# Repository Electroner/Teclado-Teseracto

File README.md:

# Teclado Personalizado en Español + PCB  

En este repositorio encontraras desde los datasheet de cada parte que he usado hasta los archivos originales del autocad, con todos los archivos descargados deberias ser capaz de poder crear y manufacturar este teclado sin ningun problema.

Este teclado usa un Atmega32u4 como controllador y un decodificador/Demultiplexor CD74HC154 4-a-16, Suficiente para conseguir un tiempo de respuesta igual o superior a los mejores teclados comerciales actuales (1060Hz).Pruebas realizadas con el codigo actual. Ademas se ha decido "prescindir" de un teclado numerico real, y lo que se ha hecho es conectar los numeros del numpad a  los numeros de la parte superior del teclado, por lo que las teclas tanto del numpad como los de la parte superior son los mismas, al igual con el intro y "." (Ver Esquematica).

Para el cuerpo y Plate se ha optado por una fabricacion completa de metacrilato atornillada de extremo a extremo con 28 tornillos que provocaran una sujeccion y una robustez sin igual. El diseño en todo momento de cada parte se ha realizado pensando en su mantenimiento y facilidad de reparacion.

Se ha actualizado a la version N-keyRollOver con unas modificaciones en las librerias de Keyboard.h y Keyboard.cpp

## Imagenes

Teclado Finalizado (No leds):

Teclado Finalizado (Leds):

Componentes de la PCB:

Vista Previa de la PCB:

Schematic:

Plano Plancha Superior (Plate):

## Recursos Usados

-   [Alguna Investigacion y aprendizaje](https://github.com/w4ilun/pocket-keyboard)

Y varias paginas para datos concretos como funciones en eagle,ayuda con el bootloader y ejemplos de otros teclados.

-   [Ayuda con el bootloader](https://forum.arduino.cc/t/burning-bootloader-to-custom-board-atmega32u4/890015)
-   [Ayuda con el N-key](https://forum.arduino.cc/t/how-to-program-n-key-rollover-atmega32u4/938418)

## Software Usado

-   [Editor de Layaout Teclado](http://www.keyboard-layout-editor.com/)
-   [Autocad](https://www.autodesk.es/products/autocad/overview?term=1-YEAR&tab=subscription)
-   [FreeCad](https://www.freecadweb.org/)
-   [Eagle](https://www.autodesk.com/products/eagle/free-download)
-   [Componentes Eagle](https://componentsearchengine.com/)
-   [Produccion de la PCB](https://jlcpcb.com/)
-   [Compra de los componentes](https://lcsc.com/)
-   [Corte de metacrilato (Tienda Local)](https://ecoplasticlaser.com/)

## Instalacion y Compilacion

Recomiendo el Arduino 1.8 (Legacy IDE (1.8.X)) en su version portable. 
Para poder compilar la placa y añadir los archivos personalizados vamos a seguir estos pasos:

1. En ./hardware/ meteremos la carpeta CLMKeyboard donde estan los archivos personalizados.
2. Dentro de las librerias (./libraries/Keyboard) vamos a sustituir los archivos keyboard.c y Keyboard.h
3. Dentro de arduino deberia aparacer nuestra Placa como CLM Keyboard.
4. Compilamos y subimos.

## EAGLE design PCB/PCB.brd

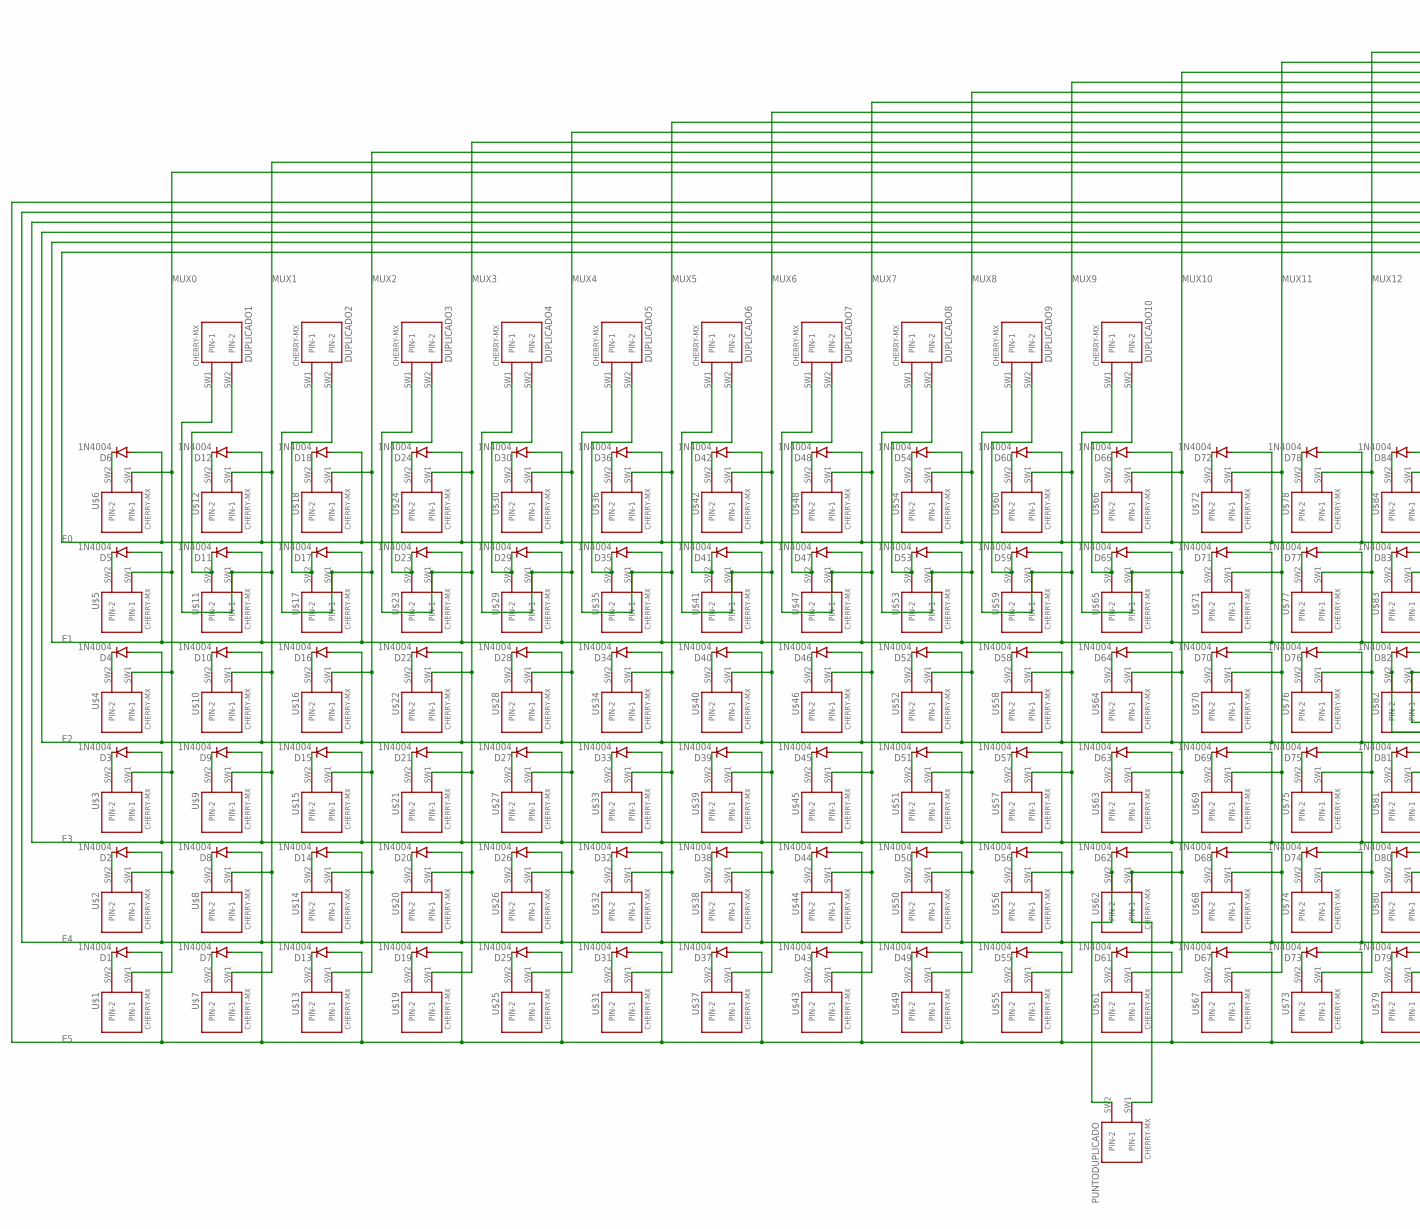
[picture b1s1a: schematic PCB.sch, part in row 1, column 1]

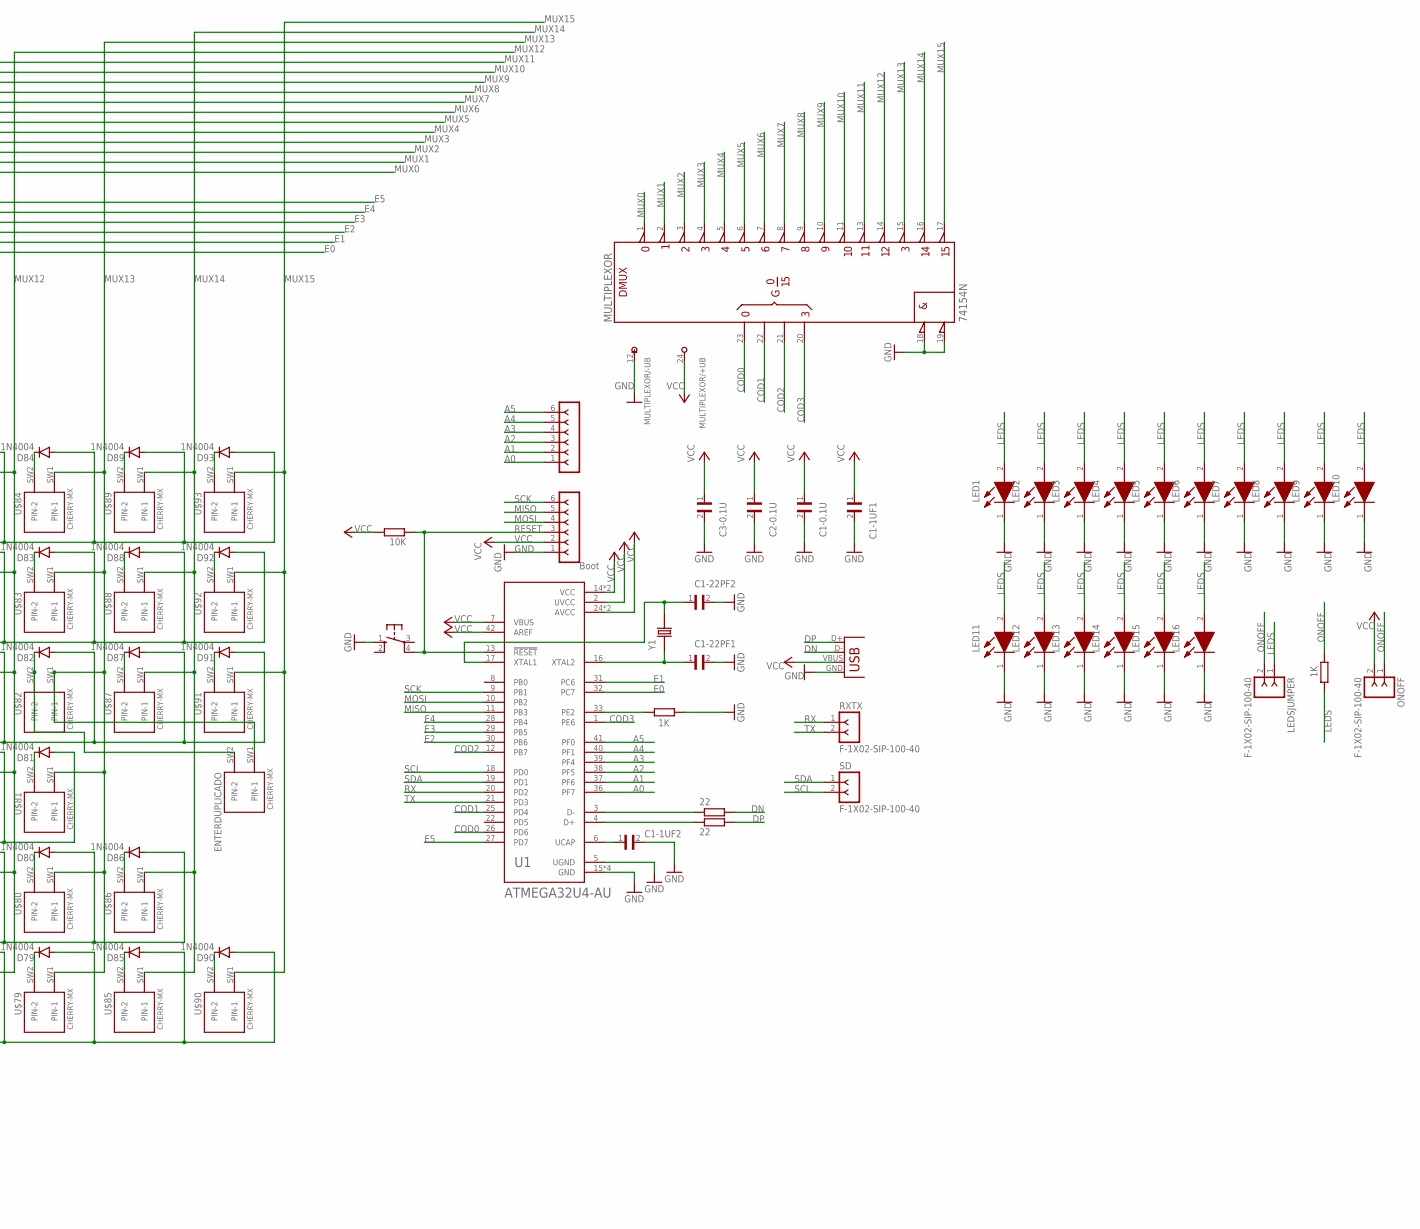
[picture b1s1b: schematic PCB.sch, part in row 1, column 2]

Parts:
ANALOG: Boot; SIP-100-06-32
BUTTON: 10-XX; B3F-10XX
C1-0.1U, C1-1UF1, C1-1UF2, C1-22PF1, C1-22PF2, C2-0.1U, C3-0.1U: RDE5C1H273J2M1H03A; CAP_RDE5C1H273J2M1H03A
D1, D2, D3, D4, D5, D6, D7, D8, D9, D10, D11, D12, D13, D14, D15, D16, D17, D18, D19, D20, D21, D22, D23, D24, D25, D26, D27, D28, D29, D30, D31, D32, D33, D34, D35, D36, D37, D38, D39, D40, D41, D42, D43, D44, D45, D46, D47, D48, D49, D50, D51, D52, D53, D54, D55, D56, D57, D58, D59, D60, D61, D62, D63, D64, D65, D66, D67, D68, D69, D70, D71, D72, D73, D74, D75, D76, D77, D78, D79, D80, D81, D82, D83, D84, D85, D86, D87, D88, D89, D90, D91, D92, D93: 1N4004; DO41-10
DUPLICADO1, DUPLICADO2, DUPLICADO3, DUPLICADO4, DUPLICADO5, DUPLICADO6, DUPLICADO7, DUPLICADO8, DUPLICADO9, DUPLICADO10: CHERRY-MX
ENTERDUPLICADO: CHERRY-MX
J3: Boot; SIP-100-06-32
LED1, LED2, LED3, LED4, LED5, LED6, LED7, LED8, LED9, LED10, LED11, LED12, LED13, LED14, LED15, LED16: ASMM-CA03-AS402; LEDM3528X200N
LEDSJUMPER: F-1X02-SIP-100-40; SIP-100-02-40
MULTIPLEXOR: 74154N; DIL24-3
ONOFF: F-1X02-SIP-100-40; SIP-100-02-40
PUNTODUPLICADO: CHERRY-MX
R1, R2: 22; 0204/7
R3, R4: 1K; 0204/7
R5: 10K; 0204/7
RXTX: F-1X02-SIP-100-40; SIP-100-02-40
SD: F-1X02-SIP-100-40; SIP-100-02-40
U1: ATMEGA32U4-AU; QFP80P1200X1200X120-44N
U$1, U$2, U$3, U$4, U$5, U$6, U$7, U$8, U$9, U$10, U$11, U$12, U$13, U$14, U$15, U$16, U$17, U$18, U$19, U$20, U$21, U$22, U$23, U$24, U$25, U$26, U$27, U$28, U$29, U$30, U$31, U$32, U$33, U$34, U$35, U$36, U$37, U$38, U$39, U$40, U$41, U$42, U$43, U$44, U$45, U$46, U$47, U$48, U$49, U$50, U$51, U$52, U$53, U$54, U$55, U$56, U$57, U$58, U$59, U$60, U$61, U$62, U$63, U$64, U$65, U$66, U$67, U$68, U$69, U$70, U$71, U$72, U$73, U$74, U$75, U$76, U$77, U$78, U$79, U$80, U$81, U$82, U$83, U$84, U$85, U$86, U$87, U$88, U$89, U$90, U$91, U$92, U$93: CHERRY-MX
X2: USB-A-H
Y1: ECS-160-20-4X; XTAL_ECS-160-20-4X

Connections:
A0: ANALOG.1, U1.36 (PF7)
A1: ANALOG.2, U1.37 (PF6)
A2: ANALOG.3, U1.38 (PF5)
A3: ANALOG.4, U1.39 (PF4)
A4: ANALOG.5, U1.40 (PF1)
A5: ANALOG.6, U1.41 (PF0)
COD0: MULTIPLEXOR.23 (A), U1.26 (PD6)
COD1: MULTIPLEXOR.22 (B), U1.25 (PD4)
COD2: MULTIPLEXOR.21 (C), U1.12 (PB7)
COD3: MULTIPLEXOR.20 (D), U1.1 (PE6)
D+: R1.1, U1.4 (D+)
D-: R2.1, U1.3 (D-)
DN: R2.2, X2.D-
DP: R1.2, X2.D+
E0: D6.A, D12.A, D18.A, D24.A, D30.A, D36.A, D42.A, D48.A, D54.A, D60.A, D66.A, D72.A, D78.A, D84.A, D89.A, D93.A, U1.32 (PC7)
E1: D5.A, D11.A, D17.A, D23.A, D29.A, D35.A, D41.A, D47.A, D53.A, D59.A, D65.A, D71.A, D77.A, D83.A, D88.A, D92.A, U1.31 (PC6)
E2: D4.A, D10.A, D16.A, D22.A, D28.A, D34.A, D40.A, D46.A, D52.A, D58.A, D64.A, D70.A, D76.A, D82.A, D87.A, D91.A, U1.30 (PB6)
E3: D3.A, D9.A, D15.A, D21.A, D27.A, D33.A, D39.A, D45.A, D51.A, D57.A, D63.A, D69.A, D75.A, D81.A, U1.29 (PB5)
E4: D2.A, D8.A, D14.A, D20.A, D26.A, D32.A, D38.A, D44.A, D50.A, D56.A, D62.A, D68.A, D74.A, D80.A, D86.A, U1.28 (PB4)
E5: D1.A, D7.A, D13.A, D19.A, D25.A, D31.A, D37.A, D43.A, D49.A, D55.A, D61.A, D67.A, D73.A, D79.A, D85.A, D90.A, U1.27 (PD7)
GND: BUTTON.1 (S), C1-0.1U.2, C1-1UF1.2, C1-1UF2.2, C1-22PF1.2, C1-22PF2.2, C2-0.1U.2, C3-0.1U.2, J3.1, LED1.1 (K), LED2.1 (K), LED3.1 (K), LED4.1 (K), LED5.1 (K), LED6.1 (K), LED7.1 (K), LED8.1 (K), LED9.1 (K), LED10.1 (K), LED11.1 (K), LED12.1 (K), LED13.1 (K), LED14.1 (K), LED15.1 (K), LED16.1 (K), MULTIPLEXOR.12 (-UB), MULTIPLEXOR.18 (!G1), MULTIPLEXOR.19 (!G2), R4.1, U1.5 (UGND), U1.15 (GND), U1.23 (GND), U1.35 (GND), U1.43 (GND), X2.GND
LEDS: LED1.2 (A), LED2.2 (A), LED3.2 (A), LED4.2 (A), LED5.2 (A), LED6.2 (A), LED7.2 (A), LED8.2 (A), LED9.2 (A), LED10.2 (A), LED11.2 (A), LED12.2 (A), LED13.2 (A), LED14.2 (A), LED15.2 (A), LED16.2 (A), LEDSJUMPER.1, R3.1
MISO: J3.5, U1.11 (PB3)
MOSI: J3.4, U1.10 (PB2)
MUX0: MULTIPLEXOR.1 (0), U$1.SW1 (PIN-1), U$2.SW1 (PIN-1), U$3.SW1 (PIN-1), U$4.SW1 (PIN-1), U$5.SW1 (PIN-1), U$6.SW1 (PIN-1)
MUX1: DUPLICADO1.SW1 (PIN-1), MULTIPLEXOR.2 (1), U$7.SW1 (PIN-1), U$8.SW1 (PIN-1), U$9.SW1 (PIN-1), U$10.SW1 (PIN-1), U$11.SW1 (PIN-1), U$12.SW1 (PIN-1)
MUX2: DUPLICADO2.SW1 (PIN-1), MULTIPLEXOR.3 (2), U$13.SW1 (PIN-1), U$14.SW1 (PIN-1), U$15.SW1 (PIN-1), U$16.SW1 (PIN-1), U$17.SW1 (PIN-1), U$18.SW1 (PIN-1)
MUX3: DUPLICADO3.SW1 (PIN-1), MULTIPLEXOR.4 (3), U$19.SW1 (PIN-1), U$20.SW1 (PIN-1), U$21.SW1 (PIN-1), U$22.SW1 (PIN-1), U$23.SW1 (PIN-1), U$24.SW1 (PIN-1)
MUX4: DUPLICADO4.SW1 (PIN-1), MULTIPLEXOR.5 (4), U$25.SW1 (PIN-1), U$26.SW1 (PIN-1), U$27.SW1 (PIN-1), U$28.SW1 (PIN-1), U$29.SW1 (PIN-1), U$30.SW1 (PIN-1)
MUX5: DUPLICADO5.SW1 (PIN-1), MULTIPLEXOR.6 (5), U$31.SW1 (PIN-1), U$32.SW1 (PIN-1), U$33.SW1 (PIN-1), U$34.SW1 (PIN-1), U$35.SW1 (PIN-1), U$36.SW1 (PIN-1)
MUX6: DUPLICADO6.SW1 (PIN-1), MULTIPLEXOR.7 (6), U$37.SW1 (PIN-1), U$38.SW1 (PIN-1), U$39.SW1 (PIN-1), U$40.SW1 (PIN-1), U$41.SW1 (PIN-1), U$42.SW1 (PIN-1)
MUX7: DUPLICADO7.SW1 (PIN-1), MULTIPLEXOR.8 (7), U$43.SW1 (PIN-1), U$44.SW1 (PIN-1), U$45.SW1 (PIN-1), U$46.SW1 (PIN-1), U$47.SW1 (PIN-1), U$48.SW1 (PIN-1)
MUX8: DUPLICADO8.SW1 (PIN-1), MULTIPLEXOR.9 (8), U$49.SW1 (PIN-1), U$50.SW1 (PIN-1), U$51.SW1 (PIN-1), U$52.SW1 (PIN-1), U$53.SW1 (PIN-1), U$54.SW1 (PIN-1)
MUX9: DUPLICADO9.SW1 (PIN-1), MULTIPLEXOR.10 (9), U$55.SW1 (PIN-1), U$56.SW1 (PIN-1), U$57.SW1 (PIN-1), U$58.SW1 (PIN-1), U$59.SW1 (PIN-1), U$60.SW1 (PIN-1)
MUX10: DUPLICADO10.SW1 (PIN-1), MULTIPLEXOR.11 (10), PUNTODUPLICADO.SW1 (PIN-1), U$61.SW1 (PIN-1), U$62.SW1 (PIN-1), U$63.SW1 (PIN-1), U$64.SW1 (PIN-1), U$65.SW1 (PIN-1), U$66.SW1 (PIN-1)
MUX11: MULTIPLEXOR.13 (11), U$67.SW1 (PIN-1), U$68.SW1 (PIN-1), U$69.SW1 (PIN-1), U$70.SW1 (PIN-1), U$71.SW1 (PIN-1), U$72.SW1 (PIN-1)
MUX12: MULTIPLEXOR.14 (12), U$73.SW1 (PIN-1), U$74.SW1 (PIN-1), U$75.SW1 (PIN-1), U$76.SW1 (PIN-1), U$77.SW1 (PIN-1), U$78.SW1 (PIN-1)
MUX13: ENTERDUPLICADO.SW1 (PIN-1), MULTIPLEXOR.15 (13), U$79.SW1 (PIN-1), U$80.SW1 (PIN-1), U$81.SW1 (PIN-1), U$82.SW1 (PIN-1), U$83.SW1 (PIN-1), U$84.SW1 (PIN-1)
MUX14: MULTIPLEXOR.16 (14), U$85.SW1 (PIN-1), U$86.SW1 (PIN-1), U$87.SW1 (PIN-1), U$88.SW1 (PIN-1), U$89.SW1 (PIN-1)
MUX15: MULTIPLEXOR.17 (15), U$90.SW1 (PIN-1), U$91.SW1 (PIN-1), U$92.SW1 (PIN-1), U$93.SW1 (PIN-1)
unnamed: D4.C, U$4.SW2 (PIN-2)
unnamed: D10.C, U$10.SW2 (PIN-2)
unnamed: D16.C, U$16.SW2 (PIN-2)
unnamed: D22.C, U$22.SW2 (PIN-2)
unnamed: D5.C, U$5.SW2 (PIN-2)
unnamed: D6.C, U$6.SW2 (PIN-2)
unnamed: D28.C, U$28.SW2 (PIN-2)
unnamed: D34.C, U$34.SW2 (PIN-2)
unnamed: D40.C, U$40.SW2 (PIN-2)
unnamed: D46.C, U$46.SW2 (PIN-2)
unnamed: D11.C, DUPLICADO1.SW2 (PIN-2), U$11.SW2 (PIN-2)
unnamed: D12.C, U$12.SW2 (PIN-2)
unnamed: D52.C, U$52.SW2 (PIN-2)
unnamed: D58.C, U$58.SW2 (PIN-2)
unnamed: D64.C, U$64.SW2 (PIN-2)
unnamed: D70.C, U$70.SW2 (PIN-2)
unnamed: D17.C, DUPLICADO2.SW2 (PIN-2), U$17.SW2 (PIN-2)
unnamed: D18.C, U$18.SW2 (PIN-2)
unnamed: D76.C, U$76.SW2 (PIN-2)
unnamed: D87.C, U$87.SW2 (PIN-2)
unnamed: D91.C, U$91.SW2 (PIN-2)
unnamed: D81.C, U$81.SW2 (PIN-2)
unnamed: D23.C, DUPLICADO3.SW2 (PIN-2), U$23.SW2 (PIN-2)
unnamed: D24.C, U$24.SW2 (PIN-2)
unnamed: D75.C, U$75.SW2 (PIN-2)
unnamed: D69.C, U$69.SW2 (PIN-2)
unnamed: D63.C, U$63.SW2 (PIN-2)
unnamed: D57.C, U$57.SW2 (PIN-2)
unnamed: D29.C, DUPLICADO4.SW2 (PIN-2), U$29.SW2 (PIN-2)
unnamed: D30.C, U$30.SW2 (PIN-2)
unnamed: D51.C, U$51.SW2 (PIN-2)
unnamed: D45.C, U$45.SW2 (PIN-2)
unnamed: D39.C, U$39.SW2 (PIN-2)
unnamed: D33.C, U$33.SW2 (PIN-2)
unnamed: D35.C, DUPLICADO5.SW2 (PIN-2), U$35.SW2 (PIN-2)
unnamed: D36.C, U$36.SW2 (PIN-2)
unnamed: D27.C, U$27.SW2 (PIN-2)
unnamed: D21.C, U$21.SW2 (PIN-2)
unnamed: D15.C, U$15.SW2 (PIN-2)
unnamed: D9.C, U$9.SW2 (PIN-2)
unnamed: D41.C, DUPLICADO6.SW2 (PIN-2), U$41.SW2 (PIN-2)
unnamed: D42.C, U$42.SW2 (PIN-2)
unnamed: D3.C, U$3.SW2 (PIN-2)
unnamed: D2.C, U$2.SW2 (PIN-2)
unnamed: D8.C, U$8.SW2 (PIN-2)
unnamed: D14.C, U$14.SW2 (PIN-2)
unnamed: D47.C, DUPLICADO7.SW2 (PIN-2), U$47.SW2 (PIN-2)
unnamed: D48.C, U$48.SW2 (PIN-2)
unnamed: D20.C, U$20.SW2 (PIN-2)
unnamed: D26.C, U$26.SW2 (PIN-2)
unnamed: D32.C, U$32.SW2 (PIN-2)
unnamed: D38.C, U$38.SW2 (PIN-2)
unnamed: D53.C, DUPLICADO8.SW2 (PIN-2), U$53.SW2 (PIN-2)
unnamed: D54.C, U$54.SW2 (PIN-2)
unnamed: D44.C, U$44.SW2 (PIN-2)
unnamed: D50.C, U$50.SW2 (PIN-2)
unnamed: D56.C, U$56.SW2 (PIN-2)
unnamed: D68.C, U$68.SW2 (PIN-2)
unnamed: D59.C, DUPLICADO9.SW2 (PIN-2), U$59.SW2 (PIN-2)
unnamed: D60.C, U$60.SW2 (PIN-2)
unnamed: D74.C, U$74.SW2 (PIN-2)
unnamed: D62.C, PUNTODUPLICADO.SW2 (PIN-2), U$62.SW2 (PIN-2)
unnamed: D80.C, U$80.SW2 (PIN-2)
unnamed: D86.C, U$86.SW2 (PIN-2)
unnamed: D65.C, DUPLICADO10.SW2 (PIN-2), U$65.SW2 (PIN-2)
unnamed: D66.C, U$66.SW2 (PIN-2)
unnamed: D90.C, U$90.SW2 (PIN-2)
unnamed: D85.C, U$85.SW2 (PIN-2)
unnamed: D79.C, U$79.SW2 (PIN-2)
unnamed: D73.C, U$73.SW2 (PIN-2)
unnamed: D71.C, U$71.SW2 (PIN-2)
unnamed: D72.C, U$72.SW2 (PIN-2)
unnamed: D67.C, U$67.SW2 (PIN-2)
unnamed: D61.C, U$61.SW2 (PIN-2)
unnamed: D55.C, U$55.SW2 (PIN-2)
unnamed: D49.C, U$49.SW2 (PIN-2)
unnamed: D77.C, U$77.SW2 (PIN-2)
unnamed: D78.C, U$78.SW2 (PIN-2)
unnamed: D43.C, U$43.SW2 (PIN-2)
unnamed: D37.C, U$37.SW2 (PIN-2)
unnamed: D31.C, U$31.SW2 (PIN-2)
unnamed: D82.C, ENTERDUPLICADO.SW2 (PIN-2), U$82.SW2 (PIN-2)
unnamed: D83.C, U$83.SW2 (PIN-2)
unnamed: D84.C, U$84.SW2 (PIN-2)
unnamed: D25.C, U$25.SW2 (PIN-2)
unnamed: D19.C, U$19.SW2 (PIN-2)
unnamed: D13.C, U$13.SW2 (PIN-2)
unnamed: D88.C, U$88.SW2 (PIN-2)
unnamed: D89.C, U$89.SW2 (PIN-2)
unnamed: D7.C, U$7.SW2 (PIN-2)
unnamed: D1.C, U$1.SW2 (PIN-2)
unnamed: D92.C, U$92.SW2 (PIN-2)
unnamed: D93.C, U$93.SW2 (PIN-2)
ONOFF: LEDSJUMPER.2, ONOFF.1, R3.2
PE2: R4.2, U1.33 (PE2)
RESET: BUTTON.4 (P1), J3.3, R5.2, U1.13 (!RESET)
RX: RXTX.1, U1.20 (PD2)
SCK: J3.6, U1.9 (PB1)
SCL: SD.2, U1.18 (PD0)
SDA: SD.1, U1.19 (PD1)
TX: RXTX.2, U1.21 (PD3)
UCAP: C1-1UF2.1, U1.6 (UCAP)
VCC: C1-0.1U.1, C1-1UF1.1, C2-0.1U.1, C3-0.1U.1, J3.2, MULTIPLEXOR.24 (+UB), ONOFF.2, R5.1, U1.2 (UVCC), U1.7 (VBUS), U1.14 (VCC), U1.24 (AVCC), U1.34 (VCC), U1.42 (AREF), U1.44 (AVCC), X2.VBUS
XTAL1: C1-22PF2.1, U1.17 (XTAL1), Y1.2
XTAL2: C1-22PF1.1, U1.16 (XTAL2), Y1.1

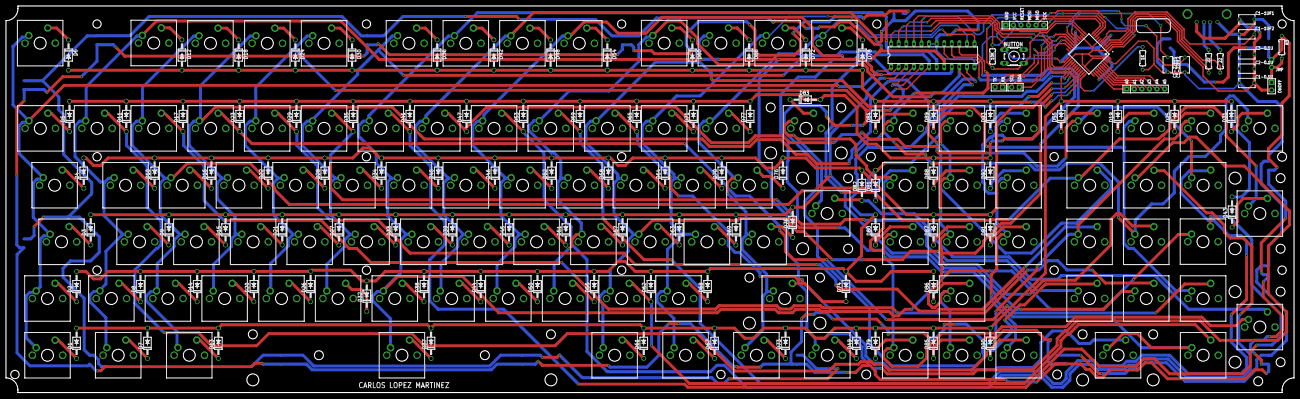
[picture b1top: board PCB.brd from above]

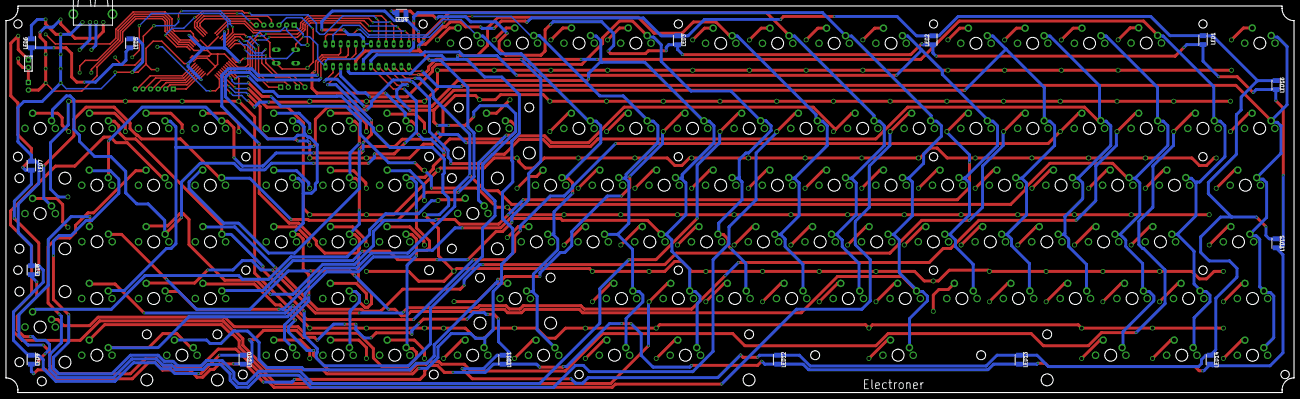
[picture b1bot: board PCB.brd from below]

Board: 2 copper layers, 431.5 x 129.5 mm, 237 parts (18 on the bottom side), 145 nets.

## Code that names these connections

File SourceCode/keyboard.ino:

#include <Keyboard.h>

#define KEY_NONE 0
#define KEY_BACKSPACE 8
#define KEY_TAB 9
#define KEY_ENTER 10
#define KEY_ESPACIO 32
#define KEY_ACENTO 39       // ´ Al lado de la Ñ
#define KEY_COMA 44         // , Al lado de la M
#define KEY_APOSTROFE 45    // ' Al lado del Backspace
#define KEY_PUNTO 46        // . Al lado del SHIFT derecho
#define KEY_MENOS 47        // - Al lado del Shift derecho
#define KEY_CERO 48
#define KEY_UNO 49
#define KEY_DOS 50
#define KEY_TRES 51
#define KEY_CUATRO 52
#define KEY_CINCO 53
#define KEY_SEIS 54
#define KEY_SIETE 55
#define KEY_OCHO 56
#define KEY_NUEVE 57
#define KEY_ENIE 59
#define KEY_EXCLAMACION 61 // ¡ Al lado del Backspace
#define KEY_ACENTOAGUDO 91  // ` Al lado de la P
#define KEY_CEDILLA 92
#define KEY_SIGNOMAS 93
#define KEY_ANGULO 96
#define KEY_A 97
#define KEY_B 98
#define KEY_C 99
#define KEY_D 100
#define KEY_E 101
#define KEY_F 102
#define KEY_G 103
#define KEY_H 104
#define KEY_I 105
#define KEY_J 106
#define KEY_K 107
#define KEY_L 108
#define KEY_M 109
#define KEY_N 110
#define KEY_O 111
#define KEY_P 112
#define KEY_Q 113
#define KEY_R 114
#define KEY_S 115
#define KEY_T 116
#define KEY_U 117
#define KEY_V 118
#define KEY_W 119
#define KEY_X 120
#define KEY_Y 121
#define KEY_Z 122
#define KEY_LSHIFT 129
#define KEY_LCONTROL 128
#define KEY_LALT 130
#define KEY_WINDOWS 131
#define KEY_RCONTROL 132
#define KEY_RSHIFT 133
#define KEY_ALTGR 134
#define KEY_ESC 177
#define KEY_CAPSLOCK 193
#define KEY_F1 194
#define KEY_F2 195
#define KEY_F3 196
#define KEY_F4 197
#define KEY_F5 198
#define KEY_F6 199
#define KEY_F7 200
#define KEY_F8 201
#define KEY_F9 202
#define KEY_F10 203
#define KEY_F11 204
#define KEY_F12 205
#define KEY_PRINTSCREEN 206
#define KEY_BLOQ 207
#define KEY_PAUSE 208
#define KEY_INS 209
#define KEY_HOME 210
#define KEY_PAGEUP 211
#define KEY_DEL 212
#define KEY_END 213
#define KEY_PAGEDOWN 214
#define KEY_FLECHADERECHA 215
#define KEY_FLECHAIZQUIERDA 216
#define KEY_FLECHAABAJO 217
#define KEY_FLECHAARRIBA 218
#define KEY_NUMLOCK 219
#define KEY_DIVISIONPAD 220
#define KEY_PORPAD 221
#define KEY_MENOSPAD 222
#define KEY_SUMAPAD 223
#define KEY_ENTERPAD 224
#define KEY_UNOPAD 225
#define KEY_DOSPAD 226
#define KEY_TRESPAD 227
#define KEY_CUATROPAD 228
#define KEY_CINCOPAD 229
#define KEY_SEISPAD 230
#define KEY_SIETEPAD 231
#define KEY_OCHOPAD 232
#define KEY_NUEVEPAD 233
#define KEY_CEROPAD 234
#define KEY_PUNTOPAD 235
#define KEY_MENOSMAYOR 236
#define KEY_CONTEXTMENU 237

const unsigned int numsCantidad = 16;   // 16 Numeros del demultiplexor
const unsigned int numsAncho = 4;       // 4 al anchura del numero en binario

const unsigned int AnchuraTeclado = 16; //Tamanio del teclado a lo largo
const unsigned int AlturaTeclado = 6;   //Tamanio del teclado a lo ancho

const unsigned int cod0 = 7; //Asignacino del pin de salida X0 (PD6)
const unsigned int cod1 = 11;  //Asignacino del pin de salida X1 (PD4)
const unsigned int cod2 = 4; //Asignacino del pin de salida X2 (PB7)
const unsigned int cod3 = 12;  //Asignacino del pin de salida X3 (PE6)

const unsigned int E0 = 13; //Asignacino del pin de Entrada E0 (PC7)
const unsigned int E1 = 5;  //Asignacino del pin de Entrada E1 (PC6)
const unsigned int E2 = 10; //Asignacino del pin de Entrada E2 (PB6)
const unsigned int E3 = 9;  //Asignacino del pin de Entrada E3 (PB5)
const unsigned int E4 = 8;  //Asignacino del pin de Entrada E4 (PB4)
const unsigned int E5 = 6;  //Asignacino del pin de Entrada E5 (PD7)

const unsigned int ESwitch[AlturaTeclado] = {E0, E1, E2, E3, E4, E5}; // Array de lectura de Fila

const bool nums0_15[numsCantidad][numsAncho] = {{0, 0, 0, 0},
                                                {1, 0, 0, 0},
                                                {0, 1, 0, 0},
                                                {1, 1, 0, 0},
                                                {0, 0, 1, 0},
                                                {1, 0, 1, 0},
                                                {0, 1, 1, 0},
                                                {1, 1, 1, 0},
                                                {0, 0, 0, 1},
                                                {1, 0, 0, 1},
                                                {0, 1, 0, 1},
                                                {1, 1, 0, 1},
                                                {0, 0, 1, 1},
                                                {1, 0, 1, 1},
                                                {0, 1, 1, 1},
                                                {1, 1, 1, 1}};

const unsigned char TeclasTeclado[AlturaTeclado][AnchuraTeclado] = {{KEY_ESC,KEY_F1,KEY_F2,KEY_F3,KEY_F4,KEY_F5,KEY_F6,KEY_F7,KEY_F8,KEY_F9,KEY_F10,KEY_F11,KEY_F12,KEY_PRINTSCREEN,KEY_BLOQ,KEY_PAUSE},
                                                                    {KEY_ANGULO,KEY_UNO,KEY_DOS,KEY_TRES,KEY_CUATRO,KEY_CINCO,KEY_SEIS,KEY_SIETE,KEY_OCHO,KEY_NUEVE,KEY_CERO,KEY_APOSTROFE,KEY_EXCLAMACION,KEY_BACKSPACE,KEY_HOME,KEY_PAGEUP},
                                                                    {KEY_TAB,KEY_Q,KEY_W,KEY_E,KEY_R,KEY_T,KEY_Y,KEY_U,KEY_I,KEY_O,KEY_P,KEY_ACENTOAGUDO,KEY_SIGNOMAS,KEY_ENTER,KEY_END,KEY_PAGEDOWN},
                                                                    {KEY_CAPSLOCK,KEY_A,KEY_S,KEY_D,KEY_F,KEY_G,KEY_H,KEY_J,KEY_K,KEY_L,KEY_ENIE,KEY_ACENTO,KEY_CEDILLA,KEY_INS,KEY_NONE,KEY_NONE},
                                                                    {KEY_LSHIFT,KEY_MENOSMAYOR,KEY_Z,KEY_X,KEY_C,KEY_V,KEY_B,KEY_N,KEY_M,KEY_COMA,KEY_PUNTO,KEY_MENOS,KEY_RSHIFT,KEY_DEL,KEY_FLECHAARRIBA,KEY_NONE},
                                                                    {KEY_LCONTROL,KEY_WINDOWS,KEY_LALT,KEY_DIVISIONPAD,KEY_PORPAD,KEY_MENOSPAD,KEY_ESPACIO,KEY_SUMAPAD,KEY_RCONTROL,KEY_NUMLOCK,KEY_ALTGR,KEY_NONE,KEY_CONTEXTMENU,KEY_FLECHAIZQUIERDA,KEY_FLECHAABAJO,KEY_FLECHADERECHA}};

const unsigned long TiempoDebounce = 5;                             //Tiempo Debounce en milisegundos
bool SwitchEstado[AlturaTeclado][AnchuraTeclado] = {false};         //Estado de la lectura de la fila
bool SwitchEstadoAntiguo[AlturaTeclado][AnchuraTeclado] = {false};  //Estado Anterior de la Tecla
unsigned long Debounce[AlturaTeclado][AnchuraTeclado] = {0};        //Tiempo de Bounce de la fila

void setup()
{
    pinMode(cod0, OUTPUT);
    pinMode(cod1, OUTPUT);
    pinMode(cod2, OUTPUT);
    pinMode(cod3, OUTPUT);

    pinMode(E0, INPUT_PULLUP);
    pinMode(E1, INPUT_PULLUP);
    pinMode(E2, INPUT_PULLUP);
    pinMode(E3, INPUT_PULLUP);
    pinMode(E4, INPUT_PULLUP);
    pinMode(E5, INPUT_PULLUP);
}

void loop()
{
    bool SwicthEstadoRapido;
    for (int i = 0; i < AnchuraTeclado; i++)
    {
        digitalWrite(cod0, nums0_15[i][3]);
        digitalWrite(cod1, nums0_15[i][2]);
        digitalWrite(cod2, nums0_15[i][1]);
        digitalWrite(cod3, nums0_15[i][0]);
        for (int k = 0; k < AlturaTeclado; k++)
        {
            SwicthEstadoRapido = !(digitalRead(ESwitch[k]));
            if (SwicthEstadoRapido && !SwitchEstadoAntiguo[k][i] && (millis() - Debounce[k][i]) > TiempoDebounce)
            {
                Debounce[k][i] = millis();
                SwitchEstadoAntiguo[k][i] = SwicthEstadoRapido;
                Keyboard.press(TeclasTeclado[k][i]);
            }
            else if (!SwicthEstadoRapido && SwitchEstadoAntiguo[k][i] && (millis() - Debounce[k][i]) > TiempoDebounce)
            {
                Debounce[k][i] = millis();
                SwitchEstadoAntiguo[k][i] = SwicthEstadoRapido;
                Keyboard.release(TeclasTeclado[k][i]);

            }
            SwitchEstado[k][i] = SwicthEstadoRapido;
        }
    }
}

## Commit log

2021-06-18 Create LICENSE
2021-07-24 Rename PCB3.brd to PCB.brd
2021-07-24 Rename PCB3.sch to PCB.sch
2021-09-15 Create Makefile
2021-11-04 Explication of Execution.txt
2022-01-30 Fixed Stabilizers Size for plate and Updates .dxf of all dwg
2022-01-30 Finished Revision 2022
2023-08-03 Update keyboard.ino
    Fixed Nums order
2024-05-07 Update keyboard.ino
    Fixed pin order
2024-05-07 Update README.md
    Added an explanation to upload code

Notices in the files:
parts and their libraries:
con-headers-jp: Copyright (C) 2008, Bob Starr
